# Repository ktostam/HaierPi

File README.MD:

# HaierPi

This project allows you to control HAIER heat pumps. 
## Tested with
1. AU082FYCRA(HW)
2. AU162FYCRA(HW)

All tests were performed on a pump with an additional ATW-a01 unit

However, it should work with all pumps that feature the YR-e27 remote control

If you have any question you can find me on discord:

[
](https://discord.gg/dVXmAfWt3P)

## Patrons
- Radek Michalowski

## Contributors
- @kocur on discord channel
- @Radek on discord channel

## Donation
If you like My work and want to support my work, you can:

Or if you from Poland:

## HARDWARE

## PCB
PCB layout is designed for both RaspberryPi zeroW and NanoPi neo 1.4.

### PCB 1.1
The revised version of the PCB (1.1) no longer has mislabeling. In addition, one of the leds and the button is now also connected to the RPi.

In the future, HaierPi will support only NanoPi

### Component List

| Symbol        | Value            | Footprint        |
|---------------|------------------|------------------|
| J1            | ADC-002          | ADC-002          |
| H3-H4         | JST XH 3         | JST-XH-TH-3-2.5  |
| POMPA,YR-E27  | JST XH 4         | JST-XH-TH-4-2.5  |
| CON1-CON3     | DG308-2.54/2     |                  |
| R1-R4         | 1K               | SMD 0805         |
| R5-R8,R10-R12 | 4.7K             | SMD 0805         |
| R9            | 120              | SMD 0805         |
| R13-R15       | 0                | SMD 0805         |
| R16-R17       | 330              | SMD 0805         |
| C1            | 104              | SMD 0805         |
| LED1          | RED              | SMD 0805         |
| LED2          | GREEN            | SMD 0805         |
| D1-D4         | 1N4007W          | SOD-123          |
| D5-D7         | SMAJ12CA         | DO214AC          |
| REL1          | N4078-2C-5V-0.2W | N4078-2C-5V-0.2W |
| REL2-REL4     | HFD23-005-1ZS    | HFD23-005-1ZS    |
| U1            | MAX3485          | SOP-8            |

### ERRATA
In the first batch of PCB's was error
PCB descriptions of R1 and R2 are swapped places, so if you have that PCB,
you need to solder 1K resistor on R6 and 4.7 on R1

### Disclaimer
- R9 is RS485 EOL resistor. For this application don't solder it.
- Resistor R14-R15 is for choosing what type to board you want to connect (Raspberrypi/NanoPi Neo). For NanoPi, 
solder 0 Ohm resistor for powering NanoPi via GPIO. `If you connect Raspberry Pi don't solder it`, because powering RPi 
from GPIO bypasses builtin protections. I will be work but its not safe. If you connecting Raspberry Pi zero W, connect
`J2`(GND) to `PP6` pad, and `J3`(+5V) to `PP1` pad. 

### Raspberry Pi
if you want to use the script on the raspberry pi, you need to add the following settings to `config.txt`:

```shell
dtoverlay=w1-gpio,gpiopin=4
dtoverlay=pi3-disable-bt
enable_uart=1
```
Be aware that this settings will disable bluetooth. but we need use UART0

### Nano Pi neo 1.4
Script is also tested on NanoPi neo 1.4. For now no change is required, but in future, when support for hardware
temperature sensor will be added, we need to remap some GPIO pins. Further information will be added later.

### Other platform
script needs a relay to control the data flow in order to function properly, so best choice is some sort of SBC.
At the moment there are no plans to add support for other SBCs, but maybe in future I will add support for relays controlled by Home Assistant, 
so script may running on any platform, and only need a RS485 connection.

## Wiki
Now the documentation is on the wiki (only in polish for now)  [wiki](https://wiki.haos.it)

## Translation
- en
- pl
### if you want to help create a translation into another language write me an email or on the discord channel

## Version
### 1.37
- Add charts with some parameters
- DHW without limit function run in turbo mode
- Add estimated daily energy consumption, separate for central heating and domestic hot water

### 1.35
- Add MQTT Discovery (by Radek)
- Add more option for heatingcurve
- Add Anti ON-OFF function
- Add DHW without limit function
- Add Parameters page
- Add Temperature Charts
- Minor fixes

### 1.32
- Add parameters
- Add scheduler for CH and DHW
- Add translation to polish
- Now changes to settings do not require a restart of the service
- New update script, from now all new update dont need to manualy add option in config.ini.
- Minor fixes

### 1.31
- Add function for automatic/manual control of frequency limit relay
- Add function for automatic/manual control of mode quiet/eco/turbo
- IMPORTANT: new option added in config.ini. If you're updating
  from previous version you need to add options: `log_leve = ERROR` in  `[DEFAULT]` block in `config.ini`
  `flimit = manual`, `flimit_temp = 10`, `presetautochange = manual`,`presetquiet = 10`,`presetturbo = -10` in `[SETTINGS]` block in `config.ini`
- minor fixes
### 1.30
- Add possibility to change heating curve parameters via settings page.
- IMPORTANT: new option added in config.ini. If you're updating
  from previous version you need to add option `hcslope = 0.7`, `hcpshift = 1` and `hcamp = 1` in `[SETTINGS]` block in `config.ini`
- Add chart with heating curve visualisation.
- minor fixes

### 1.26
- IMPORTANT: new option added in config.ini. If you're updating
  from previous version you need to add option `firstrun = 0` in `[DEFAULT]` block in `config.ini`
- Setting page is kinda ready. (unfortunetly you need to manualy restart HaierPi service after saving change for now)
- Added new service for display HaierPi logs via web, for better debugging. Now you don't need to login via ssh
- Now script can talk with home assistant via MQTT (for now there is no mqtt autodiscovery, so you need to add yaml configuration manualy).
- Updates only send via mqtt if something is changes, not as before - everything every 10 seconds
- TODO: add option somewhere to restart HaierPi service. (e.g. after config.ini changed via web)
- Minor fixes

### 1.18
- Add ds18b20 sensor support as outside temp sensor.
- Fixed error handling that could cause sysexit.
- Adding new update mechanism
 need to add new option in `config.ini`:
```shell
    release=master
```
- Minor fixes
### 1.1
In this release I change library to control GPIO, Iam not using RPi.GPIO anymore, there is some issue with RPi.GPIO replacement for Nano Pi, so I decided to control GPIO via system /sys/class/gpio/. This is independent from used SBC,

in `config.ini` there is new configuration for PIN:
```shell
[GPIO]
modbus=17 #17 for raspberrypi, 0 for nanopi neo
freqlimit=27 #27 for raspberrypi, 2 for nanopi neo
heatdemand=22 #22 for raspberrypi, 3 for nanopi neo
cooldemand=10 #10 for raspberrypi, 64 for nanopi neo
```

### 1.0

First release. for now, the following features are available:

- Show pump parameters
- Set DHW temperature
- Set Central Heating Temperature 
- Heating water temperature is calculated according to the heating curve
- Online update

#### disclaimer:
In this release inside and outside temperature must be provided by Home Assistant sensors.
For future release hardware sensor will be supported (ds18b20 for outside and DHT22 for inside temperature).

In this release, MQTT support is not finished

## LICENSE
 GNU Affero General Public License v3 [©Jacek Brzozowski](https://github.com/ktostam/HaierPi)

In this project I'am using:
[open-meteo](https://open-meteo.com/) - CC BY 4.0

[jquery-schedule](https://github.com/Yehzuna/jquery-schedule) - MIT License

[sweetalert2](https://github.com/sweetalert2/sweetalert2) - MIT License

[bootstrap](https://github.com/twbs/bootstrap) - MIT License

[jquery](https://github.com/jquery/jquery) - MIT License

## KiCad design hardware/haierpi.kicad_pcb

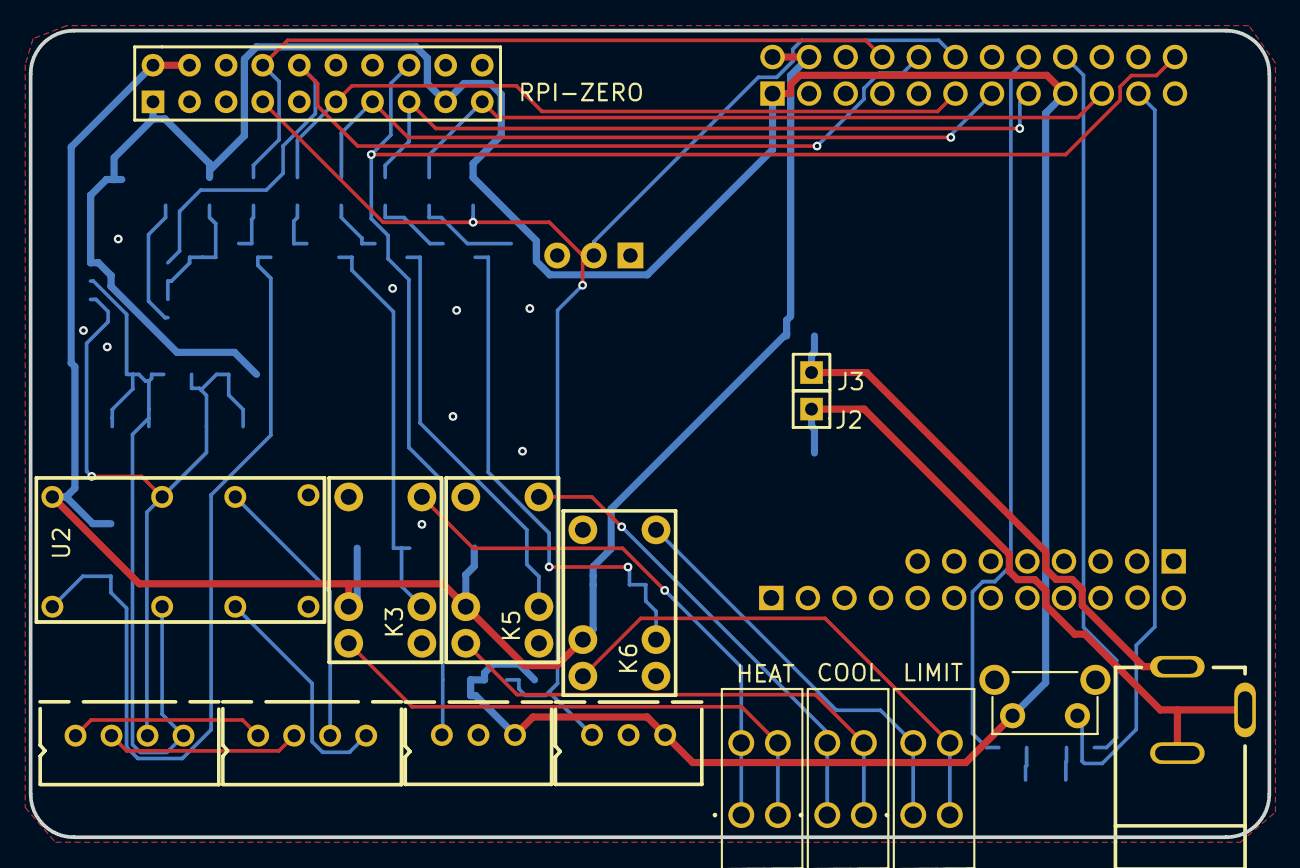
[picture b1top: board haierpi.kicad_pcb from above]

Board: 2 copper layers, 86.0 x 56.0 mm, 51 parts (0 on the bottom side), 41 nets.

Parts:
C1: 104; C0805
COOL: DG240W2.54_2P; 2X2P_2.54X5
D1, D2, D3, D4: 1N4007W_W; SOD-123_L2.8-W1.8-LS3.7-RD
D5, D6, D7: SMAJ12CA_C143115; SMA_L4.4-W2.6-LS5.0-BI
ERR: LED-0805_R; LED0805_RED
HEAT: DG240W2.54_2P; 2X2P_2.54X5
J1: JACK PCB; ADC-002
J2, J3: HDR-M-2.54_1x1; HDR-M-2.54_1X1
K3, K5, K6: HFD23-005-1ZS; RELAY-TH_HFD23-005-1ZS
LIMIT: DG240W2.54_2P; 2X2P_2.54X5
POMPA: JST XH 4; JST-XH-TH-4-2.5
Q1, Q2, Q3, Q4, Q5: 2N3904(SOT-23); SOT-23-3_L2.9-W1.3-P1.90-LS2.4-TR
R1, R2, R3, R4: 1k; R0805
R5, R6, R7, R8, R10, R11, R12: 4.7K; R0805
R9: 120; R0805
R13, R14, R15: 0; R0805
R16, R17: 330; R0805
RPI-ZERO: HDR-F-2.54_2x10; HDR-F-2.54_2X10
STAT: LED-0805_G; LED0805_GREEN
T-IN: JST XH 3; JST-XH-TH-3-2.54
T-OUT: JST XH 3; JST-XH-TH-3-2.54
U1: MAX3485; SOP-8_L4.9-W3.9-P1.27-LS6.0-BL-1
U2: N/O PINS; SMALL N4078 DUAL COMS RELAY
U3: a; NANOPI_NEO_V1.4
U5: TACTILE-SWITCH-PTH Angled; SW_TACTILE_SPST_ANGLED
U6: DS2401+T&R; TO-92-3_L4.8-W3.7-P2.54-L
YR-E27: JST XH 4; JST-XH-TH-4-2.5

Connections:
1W: R10.1, R12.1, RPI-ZERO.7, T-OUT.1, U3.12, U6.2
+3V3: C1.2, R5.2, R8.1, R10.2, R11.2, R12.2, RPI-ZERO.1, RPI-ZERO.17, T-IN.3, T-OUT.3, U1.8, U3.1, U3.17, U5.2
+5V: D1.1, D2.1, D3.1, D4.1, K3.1, K5.1, K6.1, R15.1, RPI-ZERO.2, RPI-ZERO.4, U2.8, U3.2, U3.4
A: D6.1, D7.2, POMPA.3, R8.2, R9.1, U1.6, U2.7
AOUT: U2.6, YR-E27.3
B: D5.1, D6.2, POMPA.4, R7.1, R9.2, U1.7, U2.2
BOUT: U2.3, YR-E27.4
CON1_1: HEAT.1, K3.3
CON1_2: HEAT.2, K3.5
CON2_1: COOL.1, K5.3
CON2_2: COOL.2, K5.5
CON3_1: K6.3, LIMIT.1
CON3_2: K6.5, LIMIT.2
DHT22: R11.1, RPI-ZERO.16, T-IN.1, U3.24
GND: C1.1, D5.2, D7.1, ERR.2, Q1.1, Q2.1, Q3.1, Q4.1, Q5.1, R7.2, R13.1, R14.2, RPI-ZERO.6, RPI-ZERO.9, STAT.2, T-IN.2, T-OUT.2, U1.5, U3.6, U3.9, U3.14, U3.20, U6.1
GPIO6: R1.1, RPI-ZERO.11, U3.11
GPIO13: R2.1, RPI-ZERO.13, U3.13
GPIO19: R3.1, RPI-ZERO.15, U3.15
GPIO26: R4.1, RPI-ZERO.19, U3.19
J1_1: J1.1, J3.1, R15.2
J1_2: J1.2, J1.3, J2.1, R14.1
POMPA_1: POMPA.1, YR-E27.1
POMPA_2: POMPA.2, YR-E27.2
Q5_2: Q5.2, R6.1
R1_2: Q1.2, R1.2
R2_2: Q2.2, R2.2
R3_2: Q3.2, R3.2
R4_2: Q4.2, R4.2
R16_2: R16.2, STAT.1
R17_2: ERR.1, R17.2
REL1: D1.2, Q1.3, U2.1
REL2: D4.2, K3.2, Q2.3
REL3: D3.2, K5.2, Q3.3
REL4: D2.2, K6.2, Q4.3
RX: RPI-ZERO.10, U1.1, U3.10
TX: R6.2, RPI-ZERO.8, U3.8
U1_2: Q5.3, R5.1, U1.2, U1.3
U1_4: R13.2, U1.4
U3_16: R16.1, U3.16
U3_18: R17.1, U3.18
U5_1: U3.21, U5.1

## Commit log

2023-04-18 first version
2023-04-21 work in progress update
2023-05-05 add reading from DS18b20 sensor connected directly to pcb.
2023-05-06 Fixing error handling
2023-05-06 testing
2023-05-06 fix requirements
2023-05-08 new update mechanism
2023-05-09 Use SIGINT as killsignal
2023-05-12 minor updates
2023-05-13 Version 1.21
2023-05-13 fix update.py script, now installation requirements is in virtual env
2023-05-14 typo in GetInsideTemp, GetOutsideTemp and GetHumidity
2023-05-14 version UP
2023-05-14 fix CH temp change
2023-05-14 Version
2023-05-19 Add ischange function that send mqtt message only if value has changed.
2023-05-19 settings.html update
2023-05-22 update config.ini add option 'firstrun'
2023-05-22 new weblog service for debugging without login via ssh.
2023-05-22 base.html update for now with external css and js
2023-05-23 Fix problem with tunning off everythin when turning off DHW.
2023-05-23 ver 1.27
2023-05-24 ver 1.28
2023-05-24 ver 1.29
2023-05-24 ver 1.30
2023-05-24 ver 1.31
2023-05-25 setthings.html
2023-05-29 Add support for reading local DHT22 sensor, unfortunately python has troubles with reading dht22, so I need to use external C binary
2023-06-10 Add calculating dewpoint for cooling
2023-06-10 fix in calcdewpoint function
2023-06-10 add 'import math'
2023-06-10 template fix
2023-06-10 Disable change button for cooling (for now only option is calculating dew point)
2023-06-10 update calcdewpoint
2023-06-11 changing temp in cool mode
2023-06-11 Add Twi and Two
2023-06-11 small fix
2023-10-18 rs485 communication fix
2023-10-18 typo
2023-10-19 initial change - not working
2023-10-19 something maybe work
2023-10-23 test commit
2023-10-23 I guess everything works
2023-10-24 last fix?
2023-10-24 log level defined in config.ini
2023-10-24 fix for R241 register
2023-10-25 not available outtemp can couse error with curvecalc function.
2023-10-27 Changed HA address to accept http and https prefix plus minor changes
2023-10-29 - now PyHaier is required in 0.2.8 version - add webpage with parameters (not all is correct right now). - Rename DEFAULT section to MAIN in config.ini (required for automatic update script) - from n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
2023-10-29 - I will do it later
2023-10-30 update script fix
2023-11-02 Add AntiON-OFF function Add DHW without limit function Add Central Heating and Domestic Hot Water scheduler. Few minor fixes.
2023-11-05 add missing files
2023-11-06 pl translation
2023-11-07 add more translation
2023-11-08 config updating, no need to restart service everytime
2023-11-08 update script
2023-11-08 mo translation file
2023-11-10 testupdate2
2023-11-10 test3
2023-11-11 new updates
2023-11-11 update.py update again...
2023-11-11 Version 1.32
2023-11-11 add jquery-schedule
2023-12-02 MQTT discovery 1
2023-12-02 MQTT discovery 3
2023-12-03 dhw without limit fix, change DEFAULT to MAIN in settings template
2023-12-03 VERSION 1.33
2023-12-05 added MQTT discovery
2023-12-07 dhwwl fix
2023-12-08 directly set ch temp
2023-12-08 add directly option in settings page
2023-12-08 add new translation
2023-12-08 rename dht22 bin for nanopi add dht22 bin for raspberrypi determine is running on RaspberryPi or Nano and use propper binary for dht22
2023-12-18 - New way of calculating automatic heating curve - Static curve based on slope - Manual heating curve - Possibility of direct control of water temperature - Expert mode (pump can set CH temp from 20C)
2023-12-18 add crashlog function generating dump from journal into crashlog file when any of threads is dead
2023-12-18 add MQTT discovery settings in settings page again. mqtt discovery default 0
2023-12-19 PyHaier now in version 0.3.1
2023-12-19 dht22 fix
2023-12-19 small fix in curvecalc
2023-12-20 add thitho PdPs, debug options
2023-12-21 charts
2023-12-23 change update script again...
2023-12-23 small change
2023-12-26 curvecalc fix in manual mode
2023-12-26 ver 1.35
2023-12-26 new translations
2023-12-26 Readme for 1.35
2023-12-28 crash log fix
2023-12-28 openmeteo
2023-12-28 add backup configuration, minor fixes
2023-12-28 update fix
2023-12-31 Estimate daily energy ussage of central heating and domestic hot water
2024-01-01 Restore from backup option
2024-01-01 Add TLS option for mqtt connection
2024-01-01 add CH and DHW daily usage to mqtt discovery
2024-01-01 set turbo preset in dhwwl mode, and disable auto preset change in dhwwl
2024-01-02 fix crash problem when wrong preset is set via mqtt
2024-02-04 1.37 nieskonczony
2024-02-04 1.37
2024-02-04 more changes no bump up the version
2024-07-29 Update main.py
    small bug
2024-08-19 Update main.py
    small changes for scheduler and ReadPump functions
2024-08-19 small 2
2024-08-19 small3
2024-11-18 hpiapp
2024-11-18 histeresis for thermostat and correction for kwhnow
2024-11-18 haierpi app, thermostat mode and few minor changes
2024-11-19 fix mqtt_ssl
2024-11-20 no ha discovery with hpiapp
2024-11-22 quick fix
2024-12-09 Create Dockerfile
2024-12-10 Update Dockerfile

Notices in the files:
README.MD:
AGPL License
